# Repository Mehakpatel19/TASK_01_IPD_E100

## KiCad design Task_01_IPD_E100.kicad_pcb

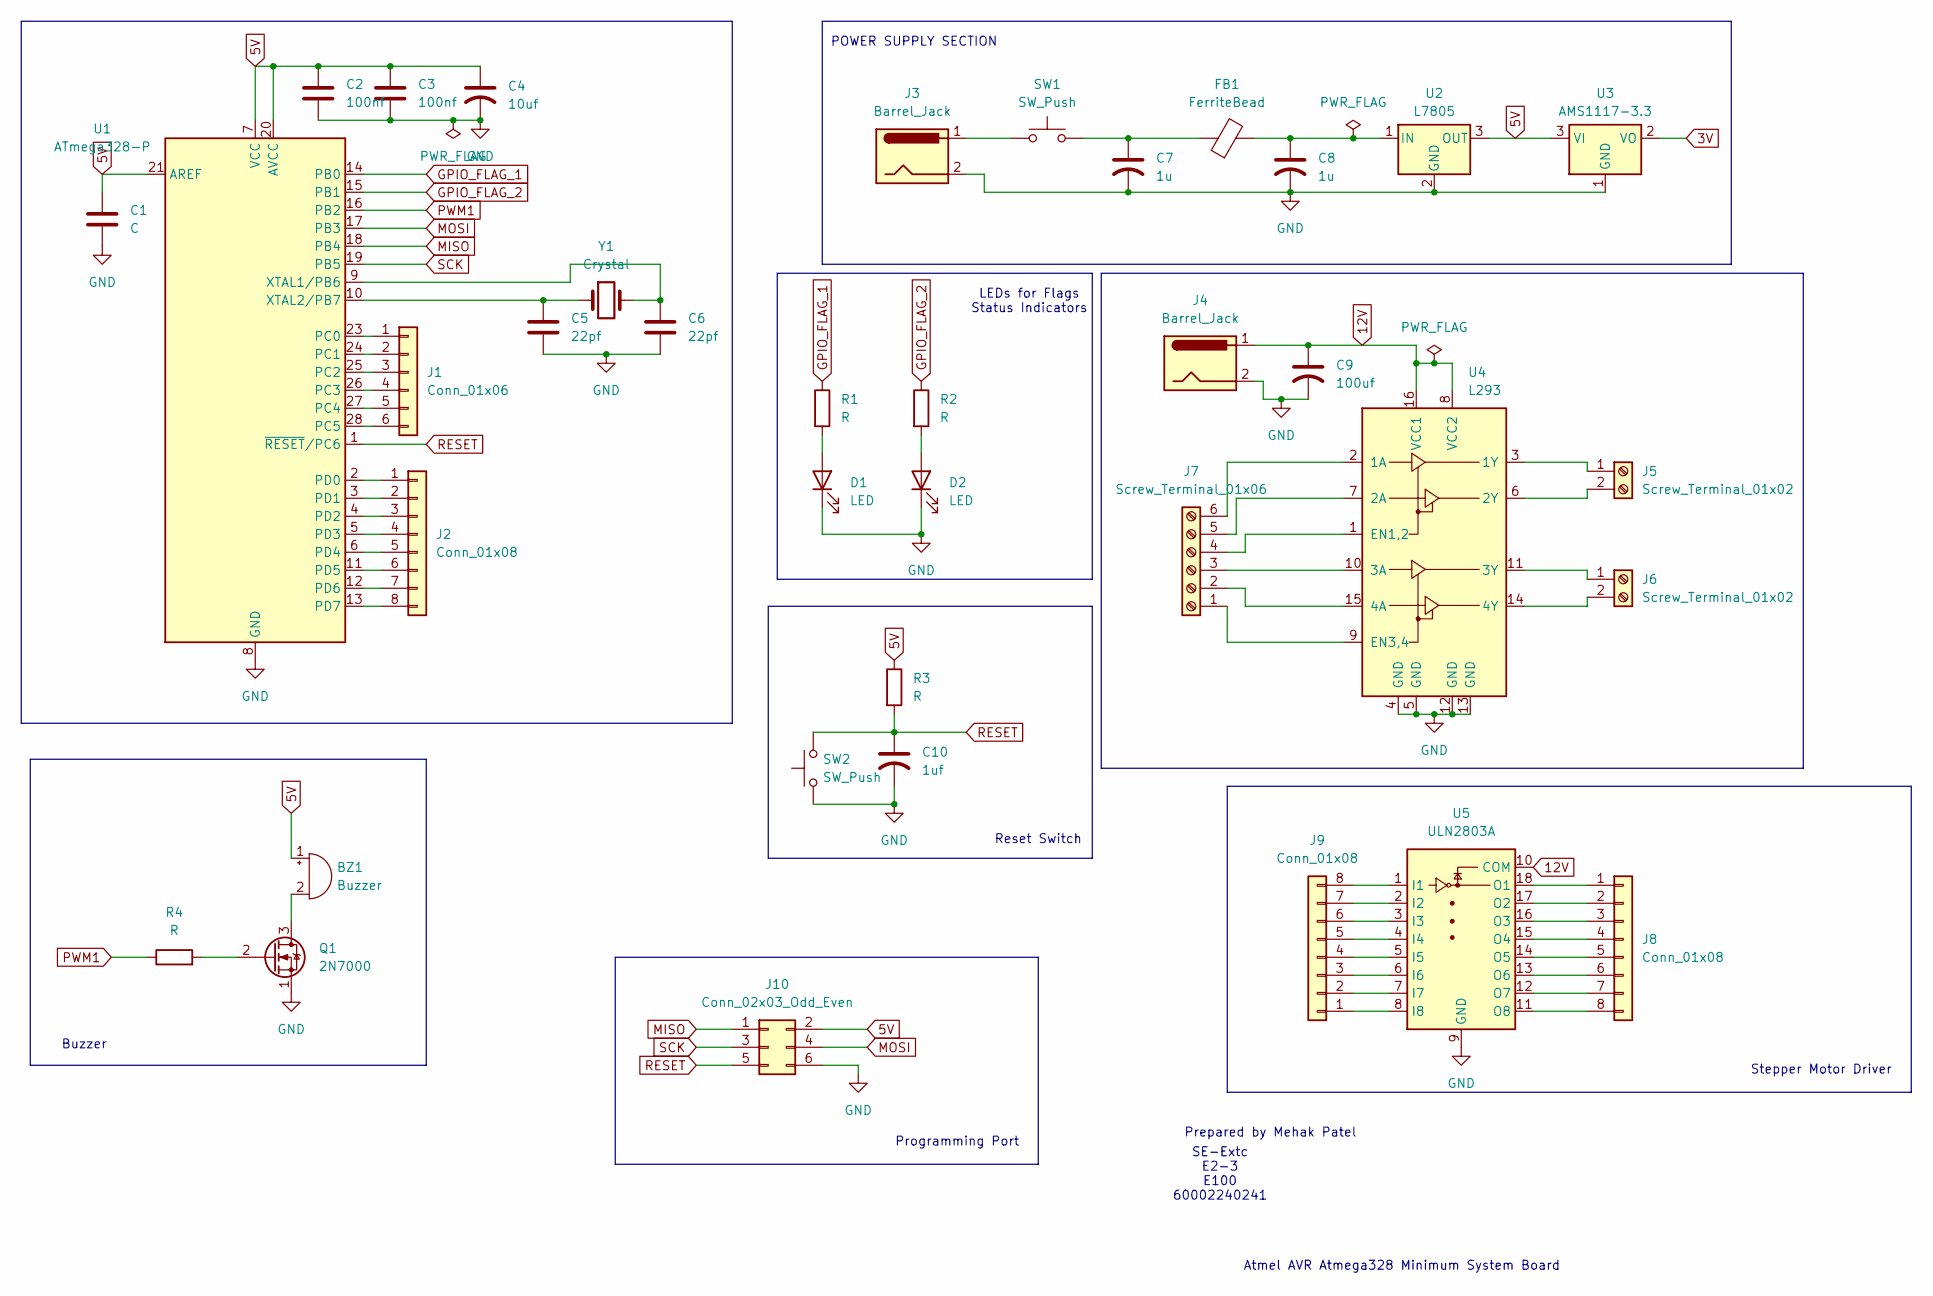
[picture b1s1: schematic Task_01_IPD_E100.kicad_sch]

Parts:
BZ1: Buzzer; Buzzer_12x9.5RM7.6
C1: C; C_0805_2012Metric_Pad1.18x1.45mm_HandSolder
C2, C3: 100nf; C_0805_2012Metric_Pad1.18x1.45mm_HandSolder
C4: 10uf; C_0805_2012Metric_Pad1.18x1.45mm_HandSolder
C5, C6: 22pf; C_0805_2012Metric_Pad1.18x1.45mm_HandSolder
C7, C8: 1u; C_0805_2012Metric
C9: 100uf; CP_Radial_D6.3mm_P2.50mm
C10: 1uf; C_Disc_D5.0mm_W2.5mm_P2.50mm
D1, D2: LED; LED_D3.0mm
FB1: FerriteBead; L_0805_2012Metric
J1: Conn_01x06; PinHeader_1x06_P2.54mm_Vertical
J2, J8, J9: Conn_01x08; PinHeader_1x08_P2.54mm_Vertical
J3, J4: Barrel_Jack; BarrelJack_Horizontal
J5, J6: Screw_Terminal_01x02; TerminalBlock_MaiXu_MX126-5.0-02P_1x02_P5.00mm
J7: Screw_Terminal_01x06; TerminalBlock_MaiXu_MX126-5.0-06P_1x06_P5.00mm
J10: Conn_02x03_Odd_Even; PinHeader_2x03_P2.54mm_Vertical
Q1: 2N7000; TO-92_Inline
R1, R2, R3, R4: R; R_Axial_DIN0207_L6.3mm_D2.5mm_P10.16mm_Horizontal
SW1, SW2: SW_Push; SW_PUSH_6mm
U1: ATmega328-P; DIP-28_W7.62mm
U2: L7805; TO-220-3_Vertical
U3: AMS1117-3.3; SOT-223-3_TabPin2
U4: L293; DIP-16_W7.62mm
U5: ULN2803A; DIP-18_W7.62mm
Y1: Crystal; Crystal_HC49-U_Vertical

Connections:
3V: U3.2 (VO)
5V: BZ1.1 (+), C1.1, C2.1, C3.1, C4.1, J10.2, R3.1, U1.7 (VCC), U1.20 (AVCC), U1.21 (AREF), U2.3 (OUT), U3.3 (VI)
12V: C9.1, J4.1, U4.8 (VCC2), U4.16 (VCC1), U5.10 (COM)
GND: C1.2, C2.2, C3.2, C4.2, C5.1, C6.2, C7.2, C8.2, C9.2, C10.2, D1.1 (K), D2.1 (K), J3.2, J4.2, J10.6, Q1.1 (S), SW2.1, U1.8 (GND), U1.22 (GND), U2.2 (GND), U3.1 (GND), U4.4 (GND), U4.5 (GND), U4.12 (GND), U4.13 (GND), U5.9 (GND)
GPIO_FLAG_1: R1.1, U1.14 (PB0)
GPIO_FLAG_2: R2.1, U1.15 (PB1)
MISO: J10.1, U1.18 (PB4)
MOSI: J10.4, U1.17 (PB3)
unnamed: BZ1.2 (-), Q1.3 (D)
unnamed: C7.1, FB1.1, SW1.2
unnamed: D1.2 (A), R1.2
unnamed: D2.2 (A), R2.2
unnamed: J1.1, U1.23 (PC0)
unnamed: J1.2, U1.24 (PC1)
unnamed: J1.3, U1.25 (PC2)
unnamed: J1.4, U1.26 (PC3)
unnamed: J1.5, U1.27 (PC4)
unnamed: J1.6, U1.28 (PC5)
unnamed: J2.1, U1.2 (PD0)
unnamed: J2.2, U1.3 (PD1)
unnamed: J2.3, U1.4 (PD2)
unnamed: J2.4, U1.5 (PD3)
unnamed: J2.5, U1.6 (PD4)
unnamed: J2.6, U1.11 (PD5)
unnamed: J2.7, U1.12 (PD6)
unnamed: J2.8, U1.13 (PD7)
unnamed: J3.1, SW1.1
unnamed: J5.1, U4.3 (1Y)
unnamed: J5.2, U4.6 (2Y)
unnamed: J6.1, U4.11 (3Y)
unnamed: J6.2, U4.14 (4Y)
unnamed: J7.1, U4.9 (EN3,4)
unnamed: J7.2, U4.15 (4A)
unnamed: J7.3, U4.10 (3A)
unnamed: J7.4, U4.1 (EN1,2)
unnamed: J7.5, U4.7 (2A)
unnamed: J7.6, U4.2 (1A)
unnamed: J8.1, U5.18 (O1)
unnamed: J8.2, U5.17 (O2)
unnamed: J8.3, U5.16 (O3)
unnamed: J8.4, U5.15 (O4)
unnamed: J8.5, U5.14 (O5)
unnamed: J8.6, U5.13 (O6)
unnamed: J8.7, U5.12 (O7)
unnamed: J8.8, U5.11 (O8)
unnamed: J9.1, U5.8 (I8)
unnamed: J9.2, U5.7 (I7)
unnamed: J9.3, U5.6 (I6)
unnamed: J9.4, U5.5 (I5)
unnamed: J9.5, U5.4 (I4)
unnamed: J9.6, U5.3 (I3)
unnamed: J9.7, U5.2 (I2)
unnamed: J9.8, U5.1 (I1)
unnamed: Q1.2 (G), R4.2
unnamed: C6.1, U1.9 (XTAL1/PB6), Y1.2
unnamed: C5.2, U1.10 (XTAL2/PB7), Y1.1
unnamed: C8.1, FB1.2, U2.1 (IN)
PWM1: R4.1, U1.16 (PB2)
RESET: C10.1, J10.5, R3.2, SW2.2, U1.1 (~RESET/PC6)
SCK: J10.3, U1.19 (PB5)

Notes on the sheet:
Buzzer
Reset Switch
SE-Extc E2-3 E100 60002240241
LEDs for Flags Status Indicators
Atmel AVR Atmega328 Minimum System Board
Stepper Motor Driver
POWER SUPPLY SECTION
Prepared by Mehak Patel
Programming Port

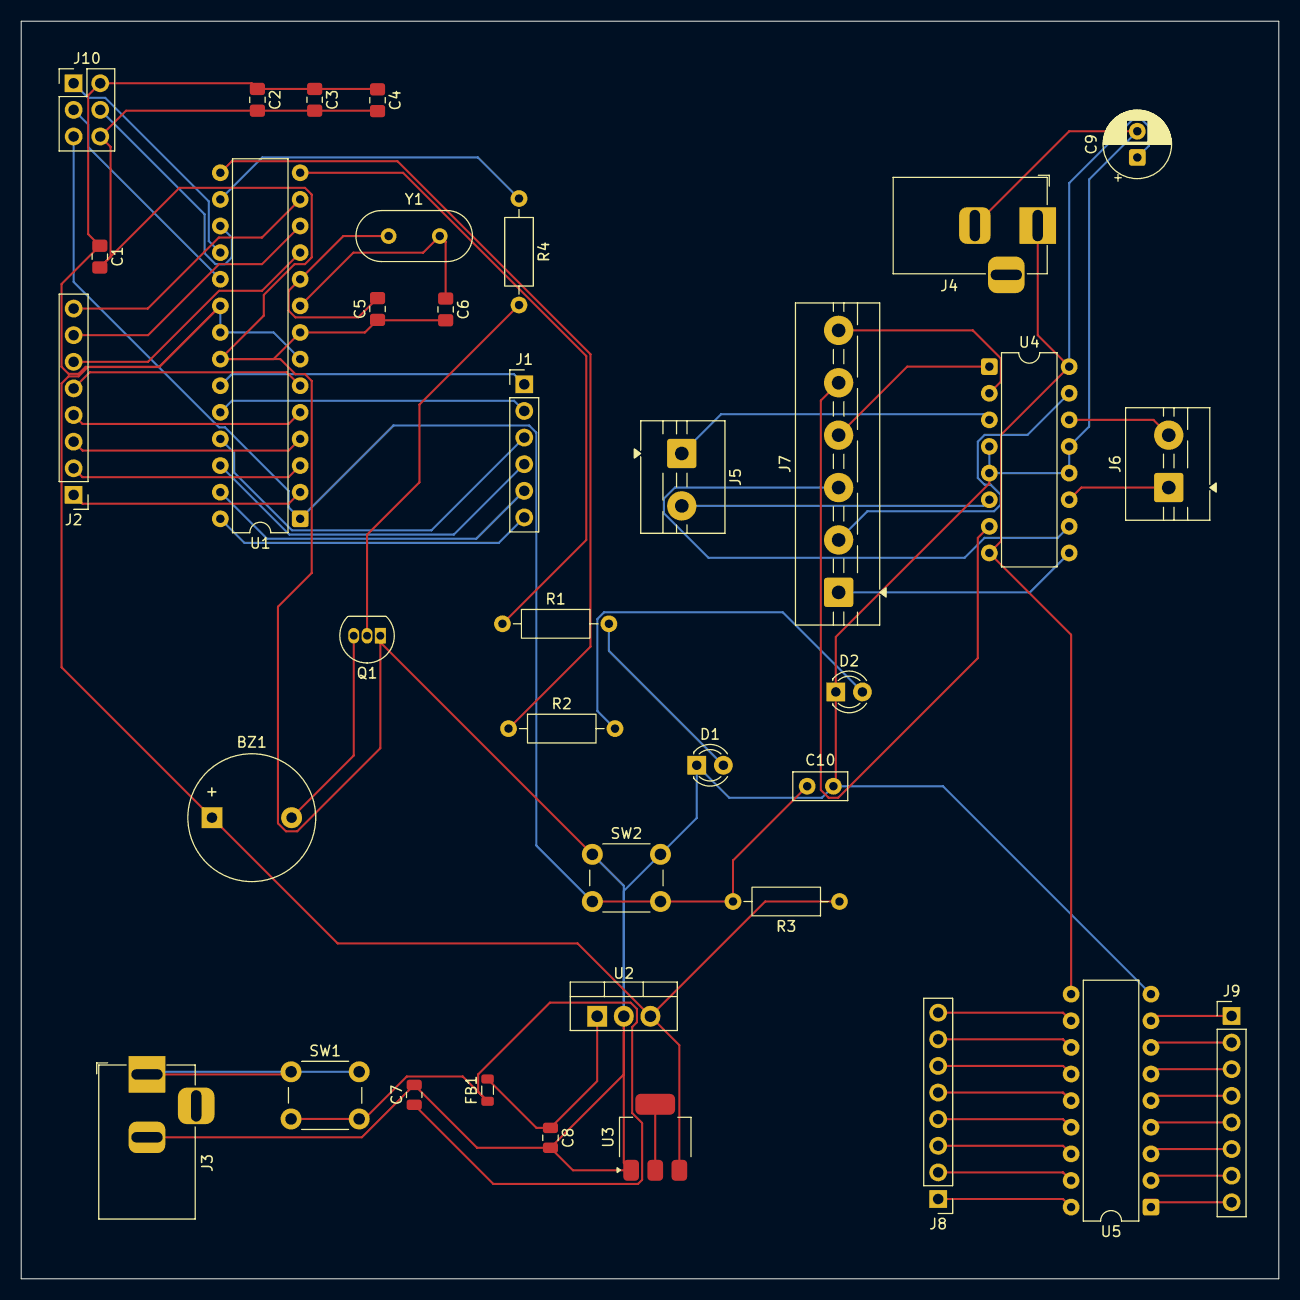
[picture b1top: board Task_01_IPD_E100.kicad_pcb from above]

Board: 2 copper layers, 120.0 x 120.0 mm, 37 parts (0 on the bottom side), 59 nets.
